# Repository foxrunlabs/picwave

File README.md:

# picWAVE

**An embedded PCM audio player built around the Microchip PIC16F1708 microcontroller, combining digital audio processing, SPI memory, and integrated analog peripherals.**

picWAVE is a custom embedded audio playback system developed in 2016–2017. It uses a PIC16F1708 microcontroller to retrieve uncompressed PCM audio from an external SPI EEPROM, convert the samples into an analog signal using the microcontroller's integrated DAC, and reconstruct the audio through an analog low-pass filter implemented with its integrated operational amplifiers.

The system includes custom hardware, embedded C firmware, and a Python utility for transferring audio recordings from a computer over a USB-to-UART interface.

The project was originally conceived as an exploration of mixed-signal embedded design, demonstrating how an inexpensive 8-bit microcontroller could perform digital audio playback while minimizing external analog components.

<p align="center">
  
  &nbsp;
  
</p>

### Key features

- **Embedded audio playback:** 44.1 kHz, 8-bit, mono PCM WAVE format.
- **Integrated analog peripherals:** Uses the PIC16F1708's internal DAC and operational amplifiers.
- **External nonvolatile storage:** Microchip 25AA1024 SPI EEPROM with 128 KiB capacity.
- **Analog reconstruction:** Fourth-order Butterworth low-pass filter implemented as two cascaded Sallen–Key stages.
- **Timer-driven playback:** Hardware timer interrupts regulate sample output.
- **Computer interface:** FTDI USB-to-UART bridge operating at 1 Mbps.
- **Python audio loader:** Transfers recordings to EEPROM without reflashing firmware.
- **Custom hardware:** Original circuit schematic, PCB layout, and bill of materials.

> **Project status:** Historical engineering project preserved for reference and portfolio purposes. The original source and hardware design have not been revalidated against current development tools.

## System architecture

picWAVE consists of three principal components: a host-side audio loader, embedded firmware, and a mixed-signal hardware platform.

```text
                 Host Computer
                ┌───────────────┐
                │ Python Loader │
                └───────┬───────┘
                        │ USB
                        ▼
                ┌───────────────┐
                │ FTDI FT230X   │
                │ USB-to-UART   │
                └───────┬───────┘
                        │ UART / RTS
                        ▼
                ┌────────────────────────┐
                │       PIC16F1708       │
                │                        │
                │  UART ──► SPI          │
                │            │           │
                │            ▼           │
                │         EEPROM         │
                │            │           │
                │            ▼           │
                │       Sample Buffer    │
                │            │           │
                │       Timer 2 Control  │
                │            │           │
                │            ▼           │
                │       Integrated DAC   │
                │            │           │
                │            ▼           │
                │     Integrated Op Amps │
                └────────────┬───────────┘
                             │
                             ▼
                    Analog Audio Output
```

### Hardware

The original design incorporates:

| Component | Function |
|---|---|
| Microchip PIC16F1708 | Main controller, SPI/UART interfaces, DAC, and operational amplifiers |
| Microchip 25AA1024 | 1 Mbit SPI EEPROM for audio storage |
| FTDI FT230X | USB-to-UART interface |
| Texas Instruments LP2985 | 3.3 V voltage regulator |
| External passive components | Analog reconstruction filters |
| Pushbutton and LEDs | Playback control and system status |

The PCB schematic and layout are available in the [`schematic/`](schematic/) directory.

### Analog audio reconstruction

A central design objective was to exploit the PIC16F1708's integrated analog peripherals rather than employ an external audio DAC and operational amplifier ICs.

The design uses the microcontroller's internal 8-bit DAC to produce a voltage proportional to each PCM sample.

The resulting staircase waveform is passed through two cascaded second-order Sallen–Key low-pass filter stages. Together, these form a fourth-order Butterworth reconstruction filter with a nominal cutoff frequency of 20 kHz.

The filter uses the microcontroller's integrated operational amplifiers in conjunction with external resistors and capacitors.

This approach reduces the number of active components required for the audio output stage and demonstrates the integration of digital and analog circuitry within a resource-constrained microcontroller.

<p align="center">
  
  <br />
  
</p>

## Firmware

The firmware is written in C using Microchip's XC8 compiler and organized around a five-state controller.

| State | Description |
|---|---|
| Idle | Waits for a playback button press or an audio upload request |
| Write WAVE | Receives audio over UART and writes it to EEPROM |
| Load WAVE | Reads and validates the WAVE header |
| Play WAVE | Reads PCM samples from EEPROM and updates the DAC |
| Done | Stops playback and disables analog peripherals |

### Audio playback

When playback is requested, the firmware reads the WAVE header from EEPROM and verifies that the recording uses the supported audio format.

It then initiates a sequential SPI read beginning at the audio data offset.

Timer 2 generates periodic interrupts that signal when the next sample should be output. The main firmware loop writes the current sample to the DAC and retrieves the following sample from EEPROM.

By keeping the EEPROM selected during playback, the firmware avoids repeatedly transmitting SPI read commands and addresses.

At the end of playback, the firmware stops Timer 2, returns the DAC to its midpoint, disables the analog peripherals, and resumes waiting for another command.

### Audio storage

Audio recordings are stored in a Microchip 25AA1024 EEPROM.

The device provides:

- 1 Mbit (128 KiB) of nonvolatile storage.
- SPI communication.
- 256-byte write pages.
- Sequential byte reads.

The available storage provides approximately **2.97 seconds of audio at 44.1 kHz, 8-bit mono**, after accounting for a standard 44-byte WAVE header.

## Audio upload utility

The repository includes a Python command-line utility that transfers a replacement audio recording to the device using an FTDI USB-to-UART interface.

The utility communicates at 1,000,000 baud and uses the RTS signal to request upload mode.

A simple application-level protocol coordinates the transfer:

1. The host asserts RTS to request an upload.
2. The microcontroller identifies itself using the `PICW` signature.
3. The host acknowledges the device and supplies the number of EEPROM pages to write.
4. The microcontroller requests successive 256-byte blocks.
5. The host transmits each block for storage in EEPROM.
6. The host releases RTS when transmission is complete.

The loader displays upload progress and elapsed transfer time.

Audio recordings can be replaced without reprogramming the PIC16F1708.

### Requirements

- Python 3
- [pySerial](https://pyserial.readthedocs.io/)
- Compatible FTDI USB-to-UART interface
- Programmed picWAVE hardware

Install the Python dependency:

```bash
python3 -m pip install pyserial
```

Upload a recording:

```bash
python3 loader/picwave.py --device /dev/ttyUSB0 audio.wav
```

Replace `/dev/ttyUSB0` with the appropriate serial device.

For example, macOS commonly uses devices named `/dev/tty.usbserial-*`, while Windows uses names such as `COM3`.

### Supported audio format

| Parameter | Requirement |
|---|---|
| Container | RIFF/WAVE |
| Encoding | Uncompressed PCM |
| Channels | Mono |
| Sample rate | 44,100 Hz |
| Sample depth | 8-bit unsigned |
| Header | Standard 44-byte PCM WAVE header |
| Maximum file size | 131,072 bytes |

The firmware expects a conventional WAVE header with a 16-byte `fmt ` chunk followed immediately by the `data` chunk.

Files containing additional metadata chunks may not be compatible.

### Firmware source

The `picWAVE.X/` directory contains the embedded firmware.

- `main.c` — Hardware initialization, playback state machine, and interrupt handling.
- `wav.c` — WAVE header validation and EEPROM transfer routines.
- `config.c` — PIC configuration settings.
- `include/` — Hardware definitions, constants, and interfaces.

### Hardware design

The `schematic/` directory contains the original circuit design and supporting files:

- `picWAVE.sch` — Circuit schematic.
- `picWAVE.brd` — PCB layout.
- `bom.xlsx` — Bill of materials.

These files document the original hardware implementation.

## Building the firmware

The firmware was developed using Microchip MPLAB X and the XC8 compiler.

Rebuilding requires:

- Microchip MPLAB X IDE.
- A version of XC8 compatible with the original source.
- PIC16F1708 device support.
- A compatible ICSP programmer.

The original project used a PICkit 3.

The repository contains the firmware source but does not include a complete MPLAB X project configuration.

To reconstruct the development environment, create a PIC16F1708 project, import the files under `picWAVE.X/src/`, and configure the compiler to use `picWAVE.X/include/`.

The original IDE and compiler versions were not recorded, and compatibility changes may be necessary when using current tools.

## Engineering considerations and limitations

picWAVE was designed as an experimental embedded system rather than a production audio player.

The preserved implementation has several characteristics worth considering when studying or reproducing the design.

**Clock and playback timing**

The firmware configures the internal oscillator for 16 MHz, while the `_XTAL_FREQ` definition specifies 32 MHz.

Additionally, the Timer 2 configuration produces a nominal playback rate of approximately 43.48 kHz at a 16 MHz oscillator frequency, rather than precisely 44.1 kHz.

These discrepancies should be resolved before reproducing or modifying the firmware.

**Audio format validation**

The firmware expects a fixed WAVE header layout and does not implement a general-purpose RIFF parser.

It also does not fully validate all relationships between chunk sizes and available EEPROM capacity.

**EEPROM transfers**

The upload protocol is intentionally simple. It does not include checksums, readback verification, or a final confirmation that all EEPROM writes completed successfully.

**Interrupt handling**

The sample-ready flag is shared between the interrupt service routine and the main execution loop. Its declaration should be reviewed for `volatile` qualification when rebuilding or modifying the firmware.

**Power management**

The firmware disables the DAC and operational amplifiers when playback finishes but does not enter a low-power sleep mode while idle.

These observations describe the preserved implementation; they are not changes incorporated into the firmware.

## Project background

picWAVE was developed in 2016–2017 as a personal exploration of embedded systems and mixed-signal electronics.

The project brought together several areas of electrical and computer engineering, including microcontroller programming, synchronous serial communications, nonvolatile memory, digital-to-analog conversion, active analog filtering, and custom PCB design.

A companion technical article, *picWAVE: Exploring Mixed Signals with a PIC*, was prepared for submission to *Nuts & Volts* magazine but was not published.

The project is preserved as an example of embedded hardware/software integration and as part of the [Fox Run Labs](https://github.com/foxrunlabs) engineering portfolio.

## License

The firmware and Python loader are released under the [MIT License](LICENSES/MIT.txt).

Hardware design files and schematics are licensed under the [CERN Open Hardware License Version 2 – Permissive (CERN-OHL-P-2.0)](LICENSES/CERN-OHL-P-2.0.txt).

Copyright © 2016 Ryan Clarke

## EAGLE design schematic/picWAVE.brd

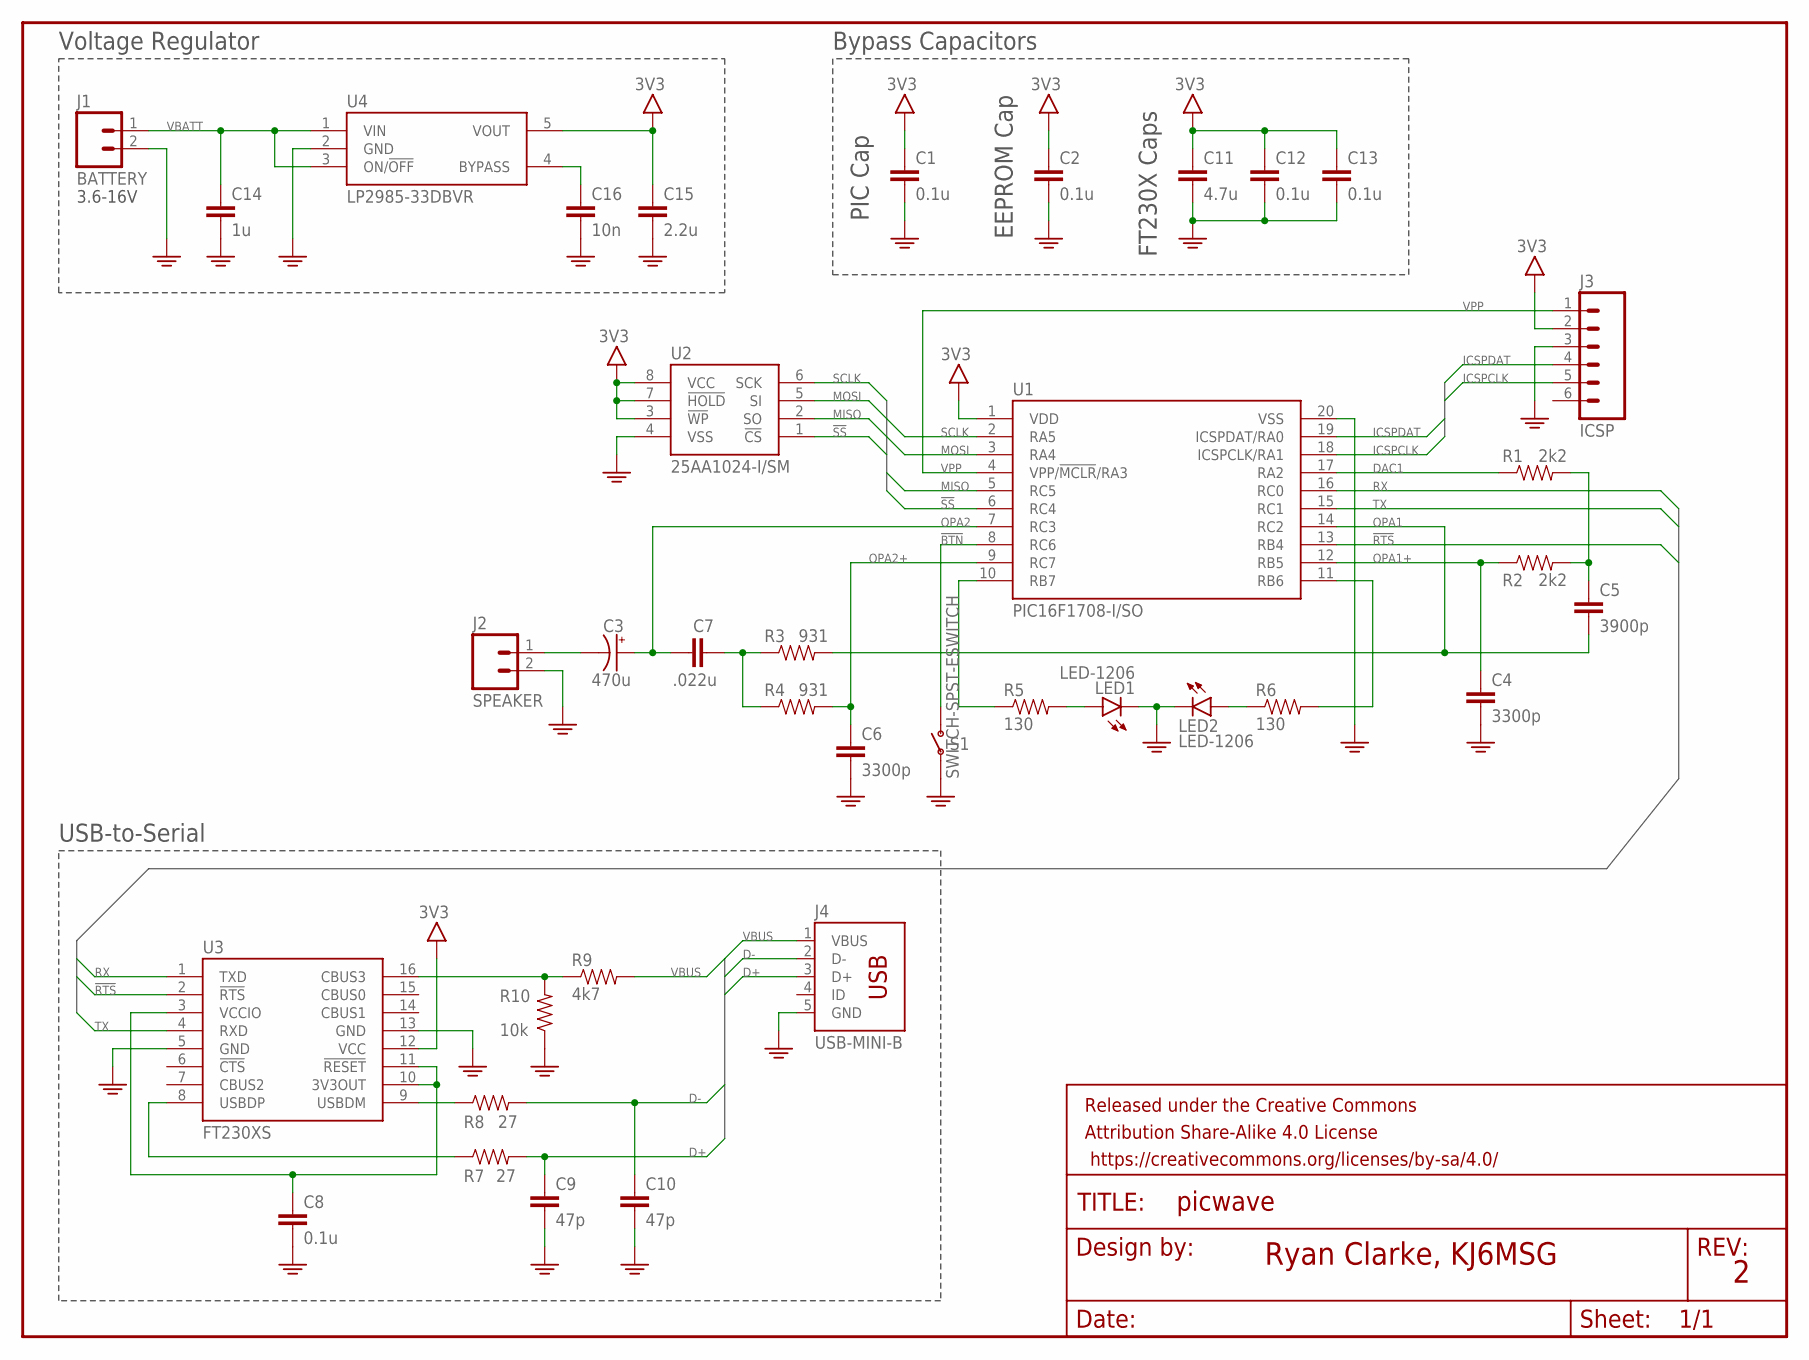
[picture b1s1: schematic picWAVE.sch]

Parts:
C1, C2: 0.1u; 1206
C3: 470u; NL1GS
C4, C6: 3300p; 1206
C5: 3900p; 1206
C7: .022u; 1206
C8, C12, C13: 0.1u; 1206@1
C9, C10: 47p; 1206@1
C11: 4.7u; 1206@1
C14: 1u; 1206
C15: 2.2u; 1206
C16: 10n; 1206
FRAME1: FRAME-LETTERNO_PACKAGE; DUMMY
J1: BATTERY; 22-05-3021
J2: SPEAKER; 22-05-3021
J3: ICSP; 1X06
J4: USB-MINI-B; XM7D-0512
LED1, LED2: LED-1206
R1, R2: 2k2; 1206
R3, R4: 931; 1206
R5, R6: 130; 1206
R7, R8: 27; 1206
R9: 4k7; 1206
R10: 10k; 1206
S1: SWITCH-SPST-ESWITCH; KS-00Q-01
U1: PIC16F1708-I/SO; SOIC-20-W
U2: 25AA1024-I/SM; SOIJ-8
U3: FT230XS; SSOP-16
U4: LP2985-33DBVR; SOT-23-5

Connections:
3V3: C1.1, C2.1, C11.1, C12.1, C13.1, C15.1, J3.2, U1.1 (VDD), U2.3 (!WP!), U2.7 (!HOLD!), U2.8 (VCC), U3.12 (VCC), U4.5 (VOUT)
!BTN!: S1.2, S1.4 (2), U1.8 (RC6)
!RTS!: U1.13 (RB4), U3.2 (!RTS!)
!SS!: U1.6 (RC4), U2.1 (!CS!)
D+: C9.1, J4.3 (D+), R7.2
D-: C10.1, J4.2 (D-), R8.2
DAC1: R1.1, U1.17 (RA2)
GND: C1.2, C2.2, C4.2, C6.2, C8.2, C9.2, C10.2, C11.2, C12.2, C13.2, C14.2, C15.2, C16.2, J1.2, J2.2, J3.3, J4.5 (GND), LED1.C, LED2.C, R10.1, S1.1, S1.3 (1), U1.20 (VSS), U2.4 (VSS), U3.5 (GND), U3.13 (GND), U4.2 (GND)
ICSPCLK: J3.5, U1.18 (ICSPCLK/RA1)
ICSPDAT: J3.4, U1.19 (ICSPDAT/RA0)
LED1: R5.1, U1.10 (RB7)
LED2: R6.2, U1.11 (RB6)
MISO: U1.5 (RC5), U2.2 (SO)
MOSI: U1.3 (RA4), U2.5 (SI)
unnamed: C16.1, U4.4 (BYPASS)
unnamed: R7.1, U3.8 (USBDP)
unnamed: C5.1, R1.2, R2.2
unnamed: C7.1, R3.1, R4.1
unnamed: C3.-, J2.1
unnamed: C8.1, U3.3 (VCCIO), U3.10 (3V3OUT), U3.11 (!RESET!)
unnamed: R8.1, U3.9 (USBDM)
unnamed: R9.1, R10.2, U3.16 (CBUS3)
unnamed: LED2.A, R6.1
unnamed: LED1.A, R5.2
OPA1: C5.2, R3.2, U1.14 (RC2)
OPA1+: C4.1, R2.1, U1.12 (RB5)
OPA2: C3.+, C7.2, U1.7 (RC3)
OPA2+: C6.1, R4.2, U1.9 (RC7)
RX: U1.16 (RC0), U3.1 (TXD)
SCLK: U1.2 (RA5), U2.6 (SCK)
TX: U1.15 (RC1), U3.4 (RXD)
VBATT: C14.1, J1.1, U4.1 (VIN), U4.3 (ON/!OFF!)
VBUS: J4.1 (VBUS), R9.2
VPP: J3.1, U1.4 (VPP/!MCLR!/RA3)

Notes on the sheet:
Ryan Clarke, KJ6MSG
Voltage Regulator
USB-to-Serial
PIC Cap
EEPROM Cap
FT230X Caps
Bypass Capacitors
3.6-16V

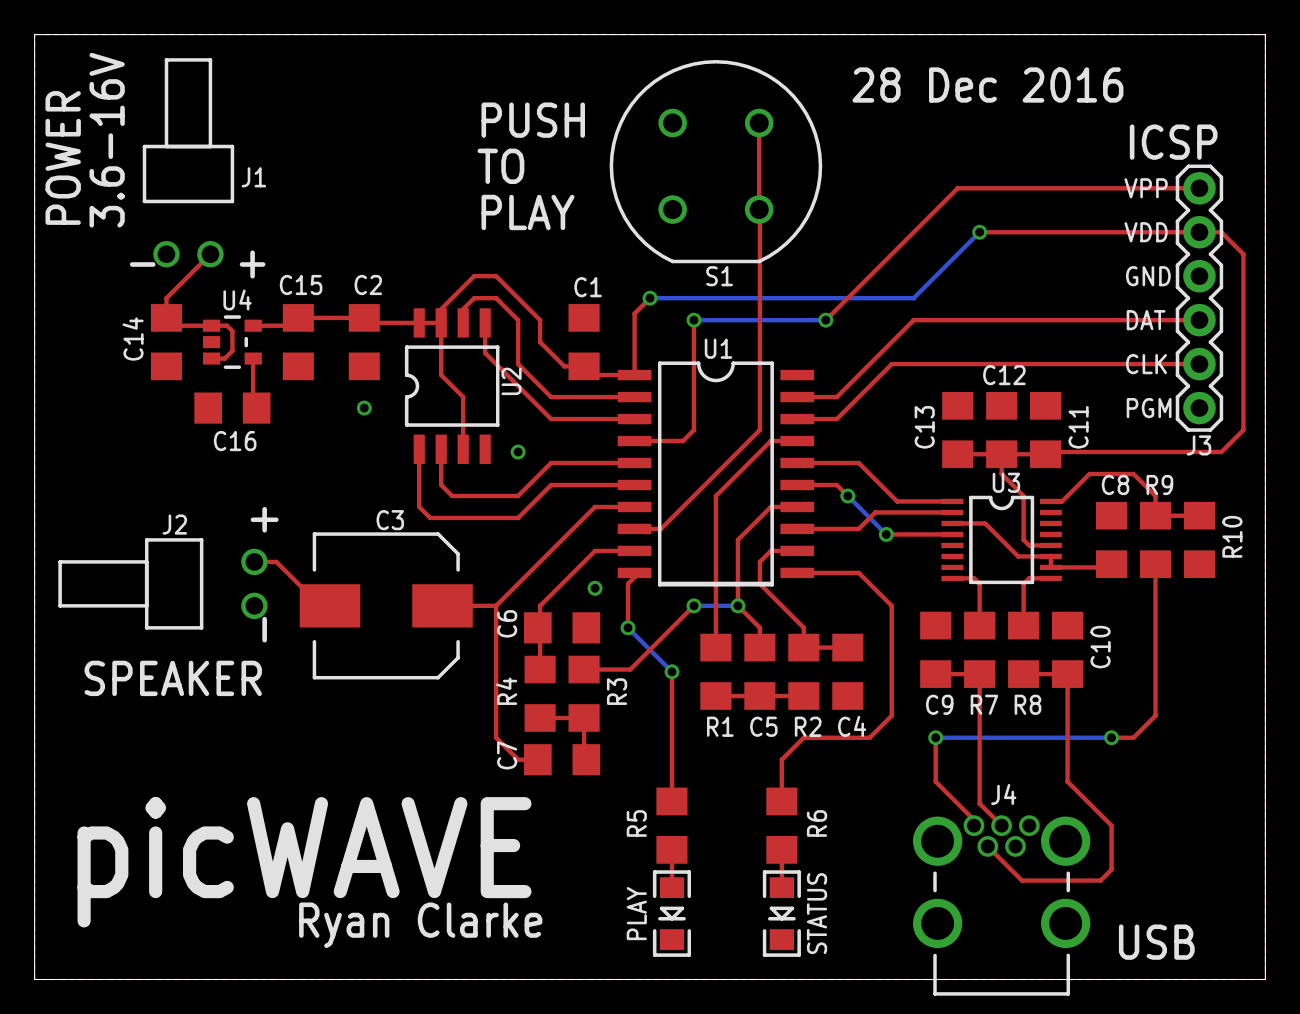
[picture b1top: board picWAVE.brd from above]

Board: 2 copper layers, 71.1 x 54.6 mm, 38 parts (0 on the bottom side), 34 nets.

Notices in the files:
parts and their libraries:
SparkFun-Aesthetics: Licensing: Creative Commons ShareAlike 4.0 International - https://creativecommons.org/licenses/by-sa/4.0
SparkFun-Aesthetics: Released under the Creative Commons Attribution Share-Alike 4.0 License
SparkFun-Aesthetics: https://creativecommons.org/licenses/by-sa/4.0
